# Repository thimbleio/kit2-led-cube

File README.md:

The Thimble LED cube kit.

hadware/ - datasheets, PCB design files

learning/ - tutorial content, intended to be viewed on learning.thimble.io

software/ - code examples written for the Arduino IDE

For more info or to subscribe, visit http://www.thimble.io

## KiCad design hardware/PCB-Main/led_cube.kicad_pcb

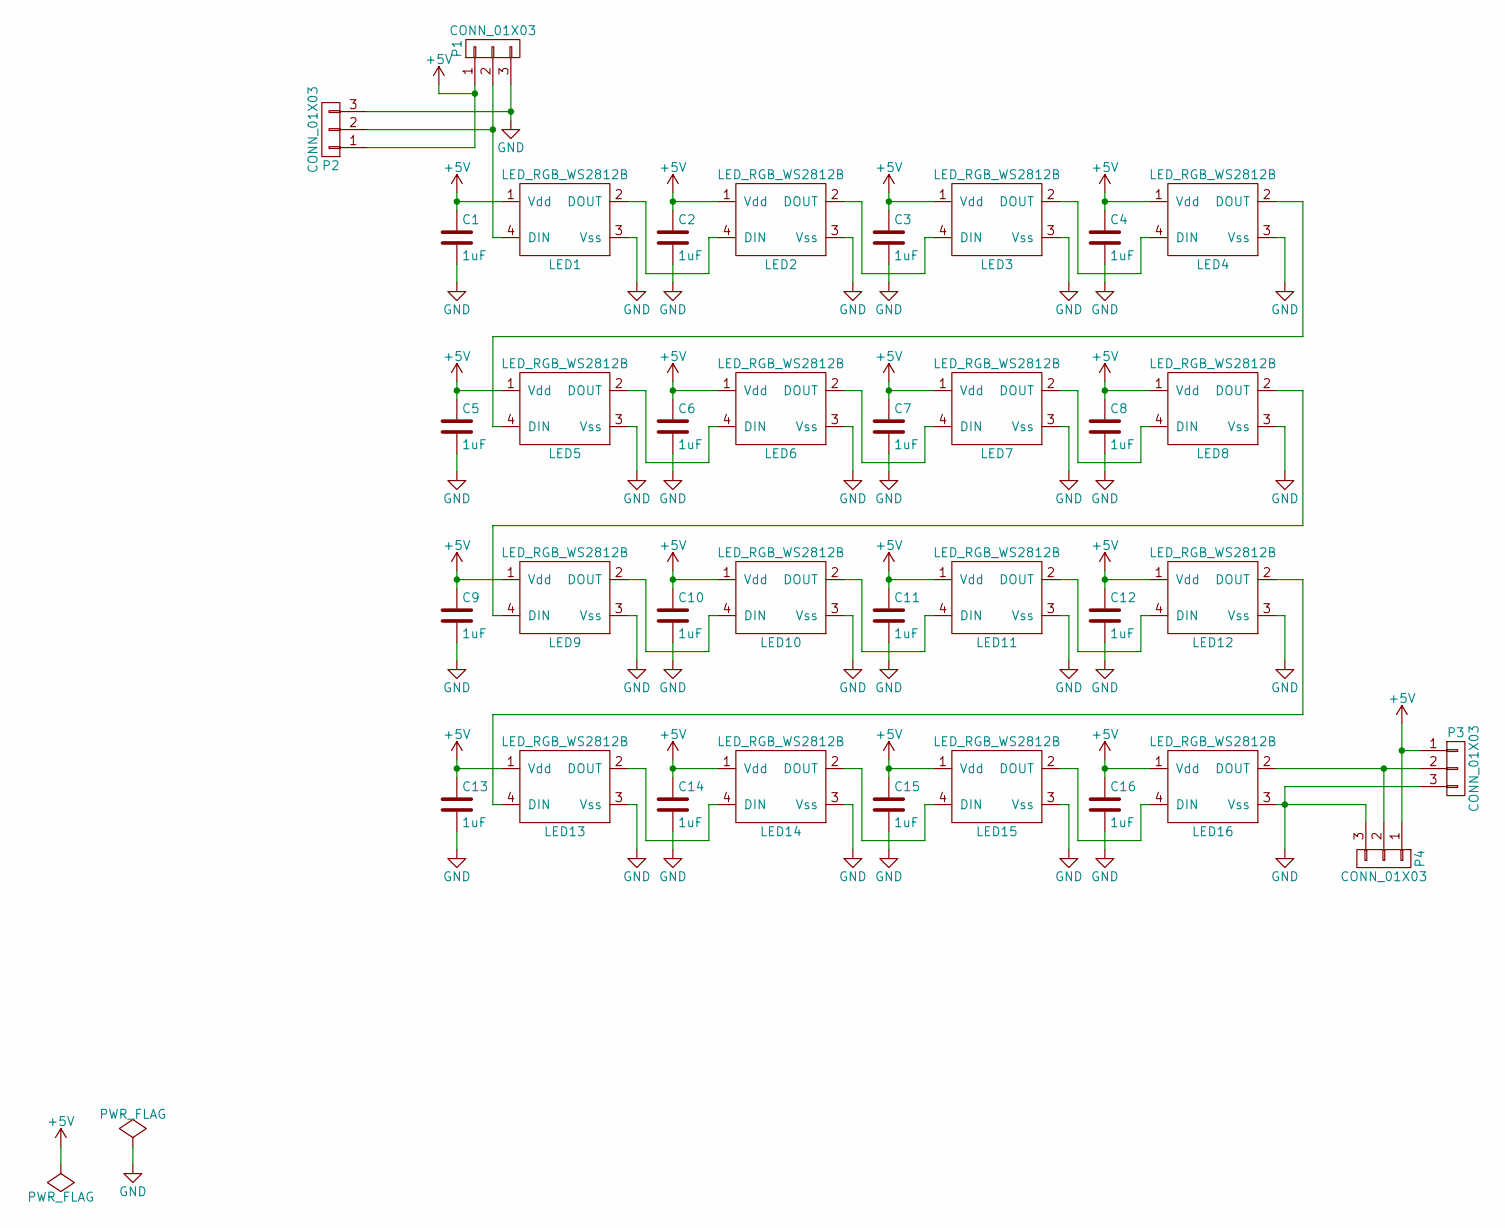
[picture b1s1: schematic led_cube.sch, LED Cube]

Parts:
C1, C3, C5, C7, C9, C11, C13, C15: 1uF; C_0603
C2, C4, C6, C8, C10, C12, C14, C16: 1uF; C_0603; MFG Part Num Value
LED1, LED2, LED3, LED4, LED5, LED6, LED7, LED8, LED9, LED10, LED11, LED12, LED13, LED14, LED15, LED16: LED_RGB_WS2812B; 5050; MFG Part Num WS2812B
P1, P2, P3, P4: CONN_01X03; Pin_Header_Straight_1x03

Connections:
+5V: C1.1, C2.1, C3.1, C4.1, C5.1, C6.1, C7.1, C8.1, C9.1, C10.1, C11.1, C12.1, C13.1, C14.1, C15.1, C16.1, LED1.1 (Vdd), LED2.1 (Vdd), LED3.1 (Vdd), LED4.1 (Vdd), LED5.1 (Vdd), LED6.1 (Vdd), LED7.1 (Vdd), LED8.1 (Vdd), LED9.1 (Vdd), LED10.1 (Vdd), LED11.1 (Vdd), LED12.1 (Vdd), LED13.1 (Vdd), LED14.1 (Vdd), LED15.1 (Vdd), LED16.1 (Vdd), P1.1, P2.1, P3.1, P4.1
GND: C1.2, C2.2, C3.2, C4.2, C5.2, C6.2, C7.2, C8.2, C9.2, C10.2, C11.2, C12.2, C13.2, C14.2, C15.2, C16.2, LED1.3 (Vss), LED2.3 (Vss), LED3.3 (Vss), LED4.3 (Vss), LED5.3 (Vss), LED6.3 (Vss), LED7.3 (Vss), LED8.3 (Vss), LED9.3 (Vss), LED10.3 (Vss), LED11.3 (Vss), LED12.3 (Vss), LED13.3 (Vss), LED14.3 (Vss), LED15.3 (Vss), LED16.3 (Vss), P1.3, P2.3, P3.3, P4.3
unnamed: LED1.2 (DOUT), LED2.4 (DIN)
unnamed: LED1.4 (DIN), P1.2, P2.2
unnamed: LED2.2 (DOUT), LED3.4 (DIN)
unnamed: LED3.2 (DOUT), LED4.4 (DIN)
unnamed: LED4.2 (DOUT), LED5.4 (DIN)
unnamed: LED5.2 (DOUT), LED6.4 (DIN)
unnamed: LED6.2 (DOUT), LED7.4 (DIN)
unnamed: LED7.2 (DOUT), LED8.4 (DIN)
unnamed: LED8.2 (DOUT), LED9.4 (DIN)
unnamed: LED10.2 (DOUT), LED11.4 (DIN)
unnamed: LED9.2 (DOUT), LED10.4 (DIN)
unnamed: LED11.2 (DOUT), LED12.4 (DIN)
unnamed: LED12.2 (DOUT), LED13.4 (DIN)
unnamed: LED13.2 (DOUT), LED14.4 (DIN)
unnamed: LED14.2 (DOUT), LED15.4 (DIN)
unnamed: LED15.2 (DOUT), LED16.4 (DIN)
unnamed: LED16.2 (DOUT), P3.2, P4.2

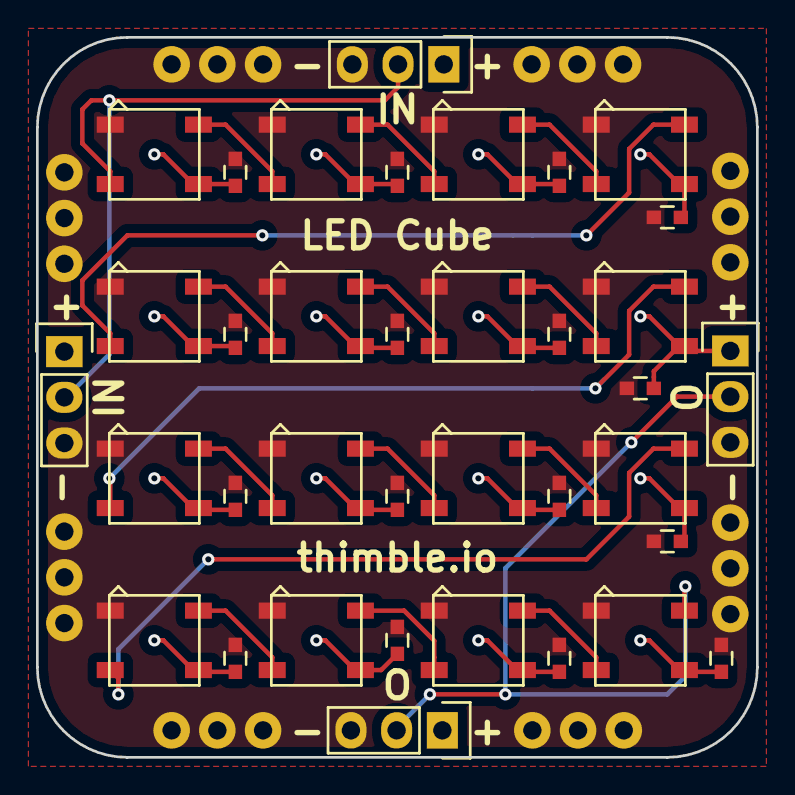
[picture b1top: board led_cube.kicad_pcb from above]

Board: 2 copper layers, 40.0 x 40.0 mm, 36 parts (0 on the bottom side), 19 nets.

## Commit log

2017-03-08 Initial public relase.
2017-03-08 Add newlines in README
2017-03-08 Add links to github for code samples
2017-03-09 Fix url for unboxing video
2017-03-09 learning: shorten title for theory section
2017-03-10 schematic: make background color white
